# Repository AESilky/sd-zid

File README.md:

# Z80 Utilities (primarily a Disassembler)

Structured to be used as a Git Module, this repository contains various Z80 utilities, with the primary utility being the Disassembler.

## Disassembler

The disassembler processes Z80 opcode and additional memory reads into Z80 source. The process is controlled by an external routine,
meaning that the disassembler accepts byte values from the external routine and indicates if more bytes are needed. It does not access
memory or file data on its own. This makes it extremely flexible in how it is integrated into a system or utility program.

A test program is provided that will feed all instructions to the disassembler and output the result to standard output. It also
accepts command line options to just disassemble selected instruction groups (single-byte, CB, DD, ED, or FD) or use byte data included
on the command line.

The test program can be used as an example to integrate the disassembler into a system.

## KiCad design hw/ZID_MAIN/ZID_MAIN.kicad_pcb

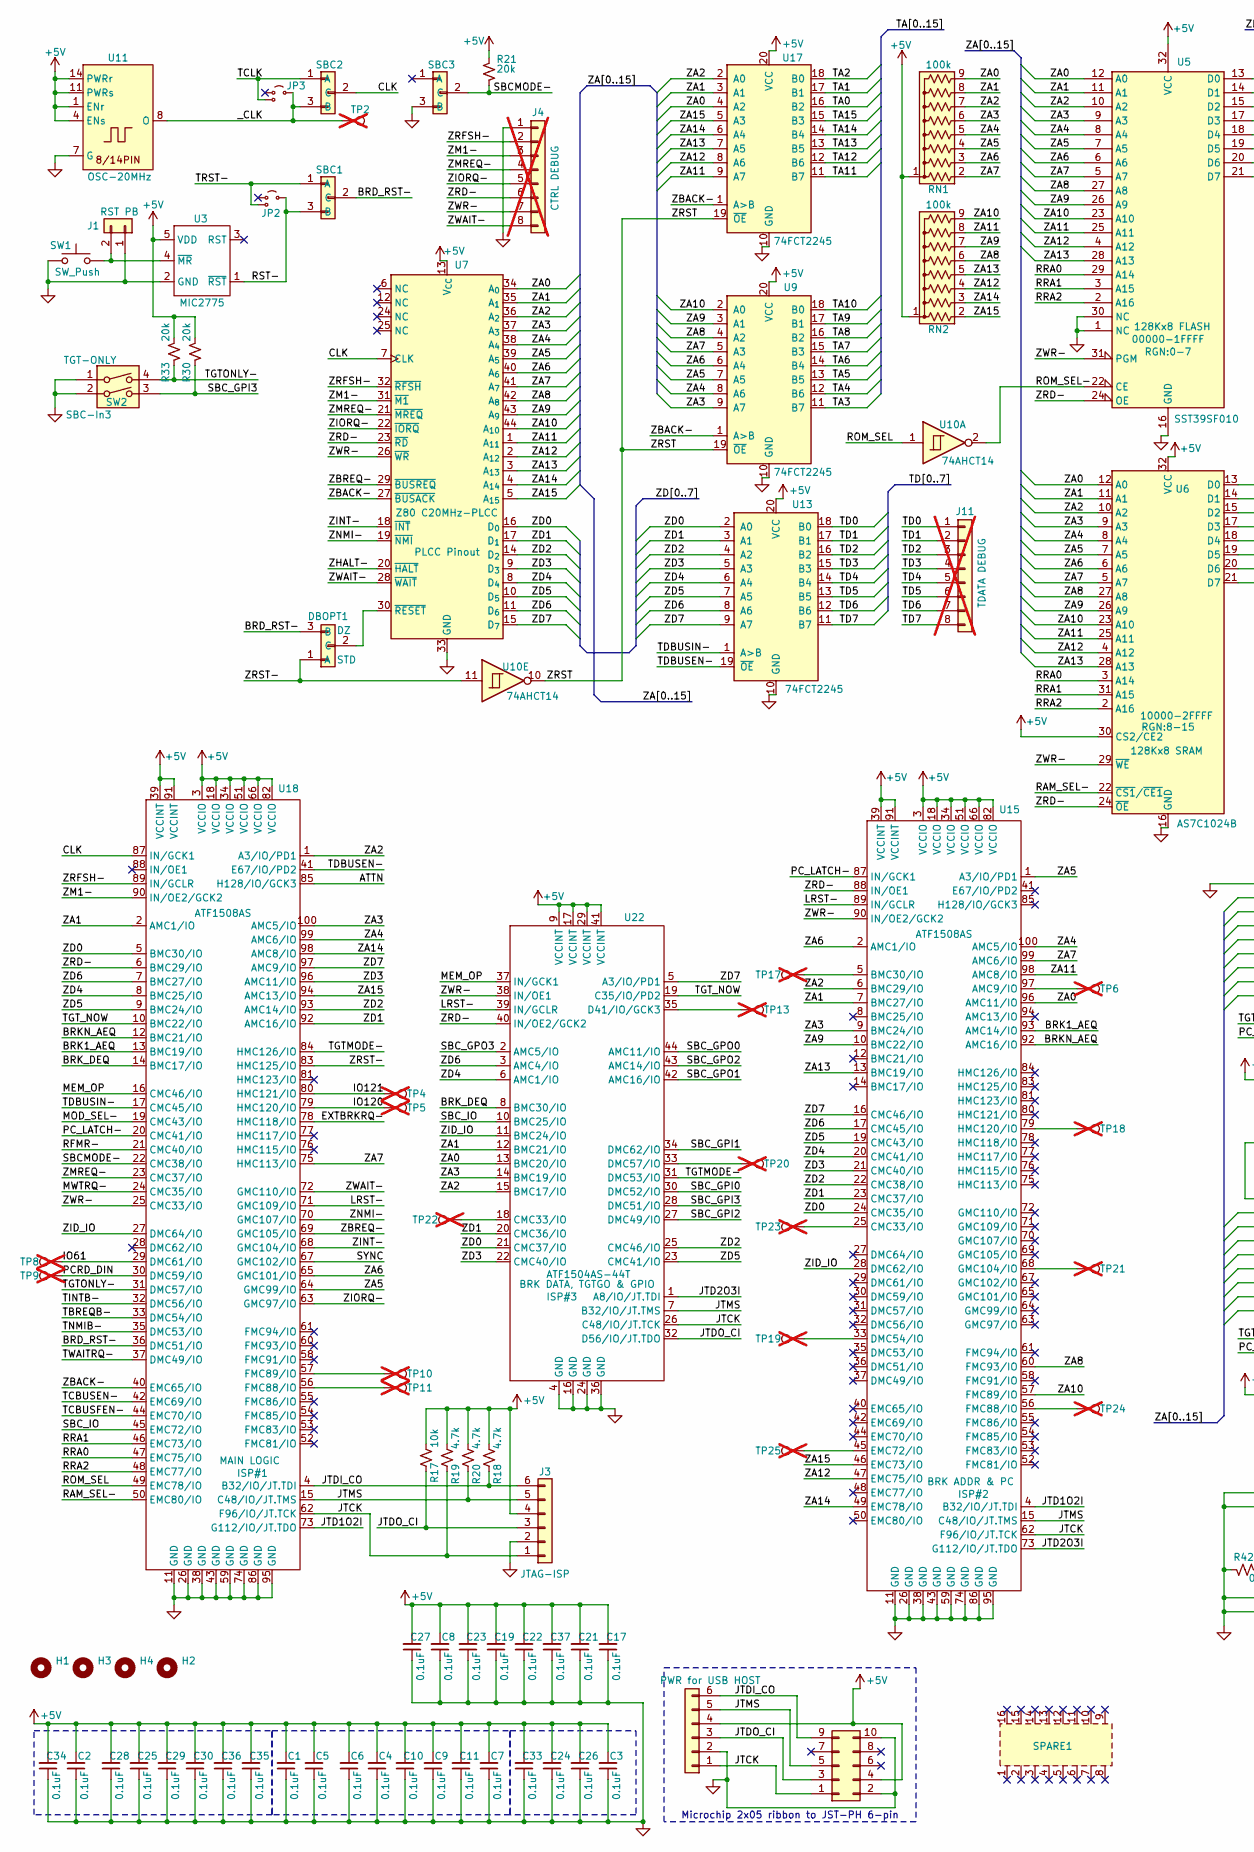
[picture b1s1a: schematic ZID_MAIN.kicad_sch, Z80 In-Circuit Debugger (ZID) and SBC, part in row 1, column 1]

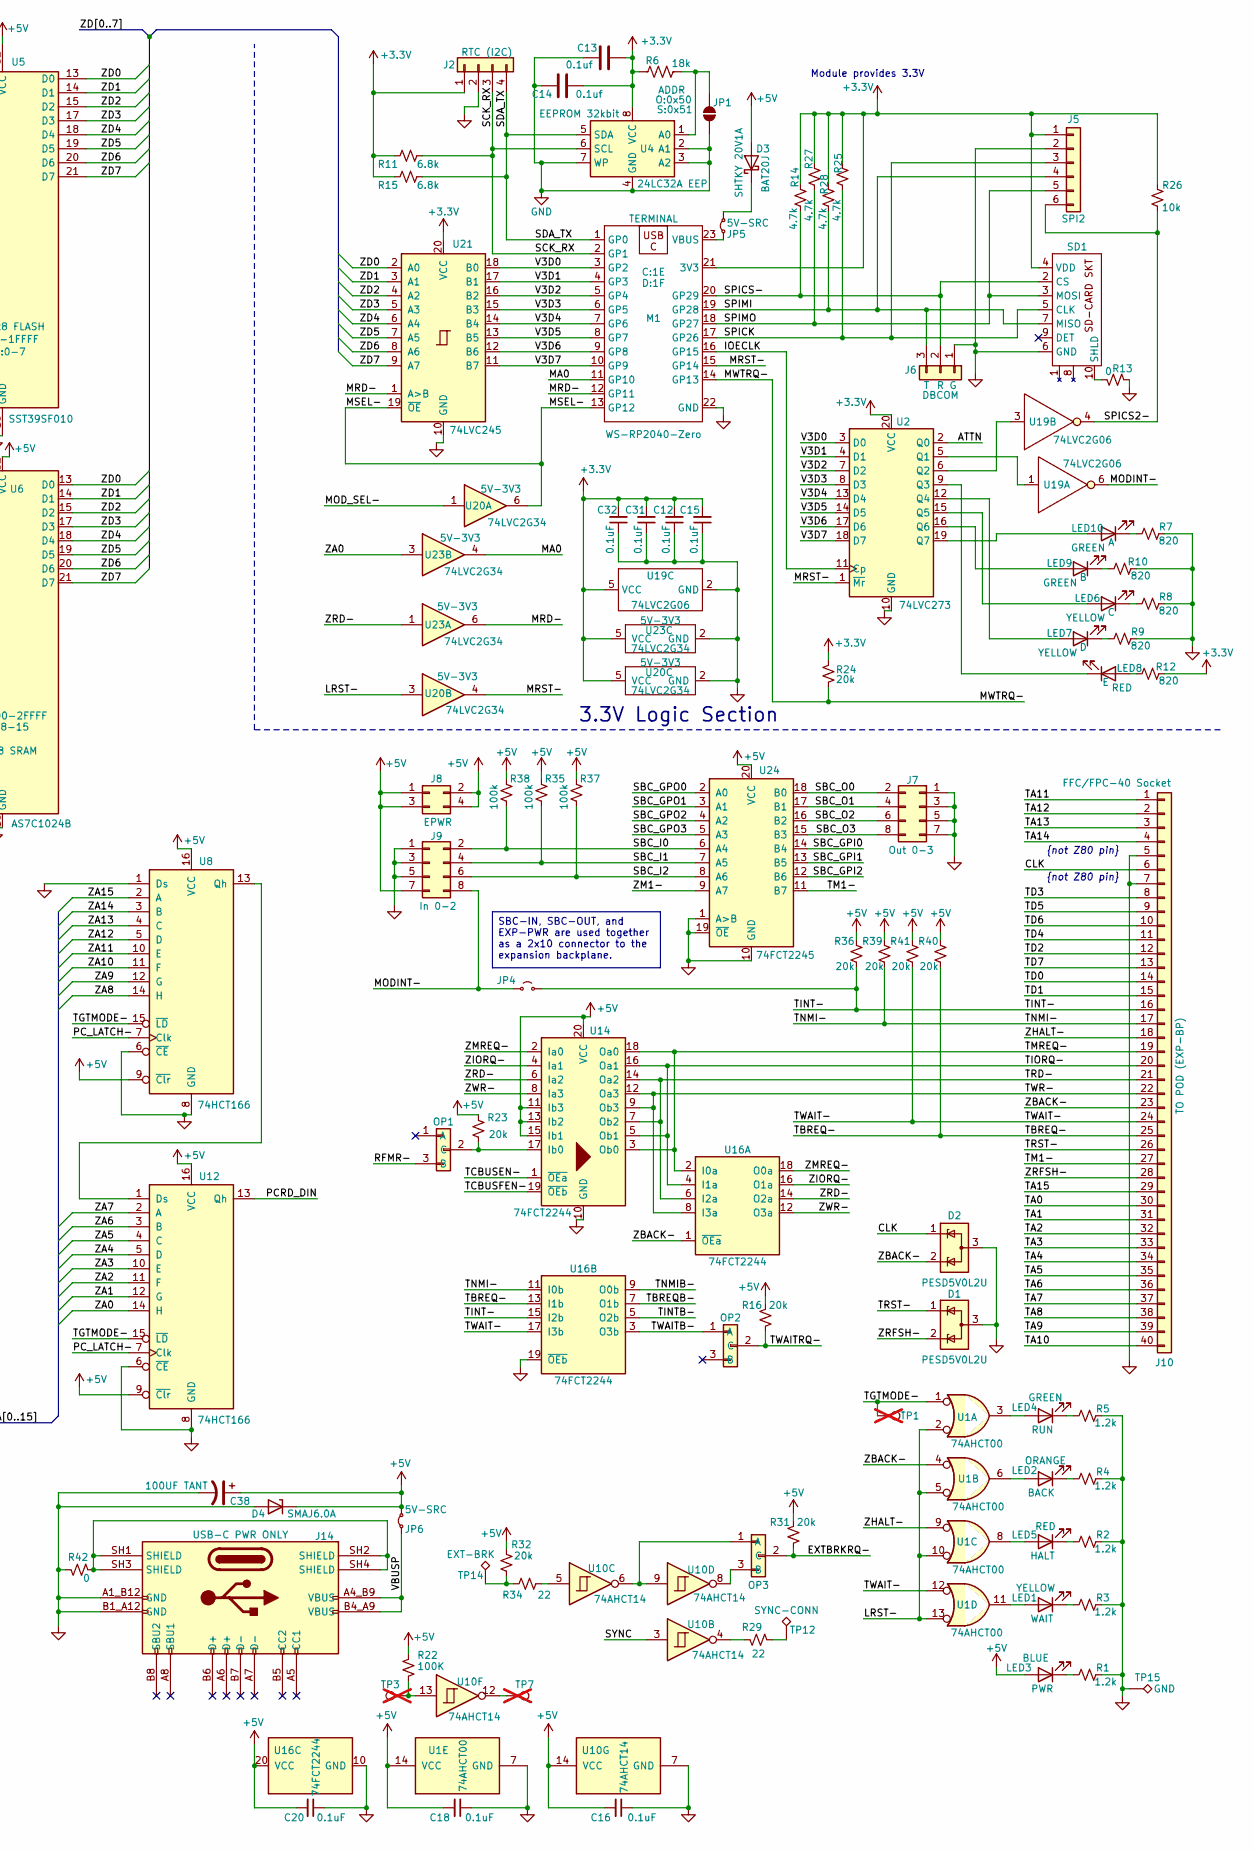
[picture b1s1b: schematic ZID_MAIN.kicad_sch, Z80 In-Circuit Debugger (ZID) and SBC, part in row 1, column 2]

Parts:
C1, C2, C3, C4, C5, C6, C7, C8, C9, C10, C11, C12, C15, C16, C17, C18, C19, C20, C21, C22, C23, C24, C25, C26, C27, C28, C29, C30, C31, C32, C33, C34, C35, C36, C37: 0.1uF; C_0603_1608Metric
C13, C14: 0.1uf; C_0603_1608Metric
C38: 100UF TANT; CP_EIA-7343-31_Kemet-D_HandSolder
D1, D2: PESD5V0L2U; SOT-323_SC-70
D3: BAT20J; D_SOD-323_HandSoldering
D4: SMAJ6.0A; D_SMA
DBOPT1: AES-Option_A-B_2mm; PinHeader_1x03_P2.00mm_Vertical
H1, H2, H3, H4: MountingHole; MountingHole_3.2mm_M3
J1: Conn 1x02 0.1" pin; PinHeader_1x02_P2.54mm_Vertical
J2: Conn 1x04 0.1" Socket; PinSocket_1x04_P2.54mm_Vertical; Part Ada-DS3231/PCF8523 RTC
J3, J5: JST-PH-K B6B; JST_PH_B6B-PH-K_1x06_P2.00mm_Vertical
J4, J11: Conn 1x08 0.1" pin; PinHeader_1x08_P2.54mm_Vertical; not fitted
J6: Conn 1x03 0.1" pin; PinHeader_1x03_P2.54mm_Vertical
J7, J9: Conn 2x04 0.1" pin; PinHeader_2x04_P2.54mm_Vertical
J8: Conn 2x02 0.1" pin; PinHeader_2x02_P2.54mm_Vertical
J10: FFC/FPC-40 Socket; CviLux_CF25401D0-05-NH_FFC-FPC-AES
J12, J14: USB-C PWR ONLY; AES-USB_C-Molex-BdTopMnt-2171790001
J13: Conn_02x05_PINHDR_2.54mm; IDC-Header_2x05_P2.54mm_Vertical
JP1: SolderJumper_2_Open; SolderJumper-2_P1.3mm_Open_RoundedPad1.0x1.5mm
JP2, JP3: Jumper_2_Small_Open_wsto-AES; PinHeader_1x03_P2.00mm_Vertical
JP4: Jumper_2_Small_Open; PinHeader_1x02_P2.00mm_Vertical
JP5, JP6: Jumper_2_Small_Bridged; PinHeader_1x02_P2.00mm_Vertical
LED1, LED6, LED7: LED YELLOW; LED_0805_2012Metric
LED2: LED ORANGE; LED_0805_2012Metric
LED3: LED BLUE; LED_0805_2012Metric
LED4, LED9, LED10: LED GREEN; LED_0805_2012Metric
LED5, LED8: LED RED; LED_0805_2012Metric
M1: WS-RP2040-Zero; RP2040_WS-ZERO-AES
OP1: AES-Option_A-B_2mm; PinHeader_1x03_P2.00mm_Vertical
OP2, OP3: pin header 1x03 0.1"; PinHeader_1x03_P2.54mm_Vertical
R1, R2, R3, R4, R5: 1.2k; R_0805_2012Metric
R6: 18k; R_0805_2012Metric
R7, R8, R9, R10, R12: 820; R_0805_2012Metric
R11, R15: 6.8k; R_0805_2012Metric
R13, R42: 0; R_0805_2012Metric
R14, R18, R19, R20, R25, R27, R28: 4.7k; R_0805_2012Metric
R16, R21, R23, R24, R30, R31, R32, R33, R36, R39, R40, R41: 20k; R_0805_2012Metric
R17, R26: 10k; R_0805_2012Metric
R22: 100K; R_0805_2012Metric
R29, R34: 22; R_0805_2012Metric
R35, R37, R38: 100k; R_0805_2012Metric
RN1, RN2: 100k; R_Array_SIP9
SBC1, SBC2, SBC3: AES-Option_A-B_2mm; PinHeader_1x03_P2.00mm_Vertical
SD1: SD-CARD Socket; AES-SDCard-GCT_MEM2075-00-140-01-A
SPARE1: SPARE-16-SOT-5_6-AES
SW1: SW_Push; AES-SW_PUSH_SMD_1P1T_NO_45x45mm-CK
SW2: SW_DIP_x02; SW_DIP_SPSTx02_Piano_CTS_Series194-2MSTN_W7.62mm_P2.54mm
TP1: TestPoint; PinHeader_1x01_P2.54mm_Vertical; not fitted
TP2: TestPoint; PinHeader_1x01_P2.00mm_Vertical; not fitted
TP3, TP4, TP5, TP6, TP7, TP8, TP9, TP10, TP11, TP13, TP17, TP18, TP19, TP20, TP21, TP22, TP23, TP24, TP25: TestPoint; TestPoint_THTPad_D1.0mm_Drill0.5mm; not fitted
TP12: SYNC-CONN; PinHeader_1x01_P2.54mm_Vertical
TP14: EXT-BRK; PinHeader_1x01_P2.54mm_Vertical
TP15: GND-CONN; PinHeader_1x01_P2.54mm_Vertical
U1: 74AHCT00; SO-14_3.9x8.65mm_P1.27mm
U2: 74LVC273; SO-20_12.8x7.5mm_P1.27mm
U3: MIC2775; SOT-23-5
U4: 24LC32A EEP; SOIC-8_3.9x4.9mm_P1.27mm
U5: SST39SF010; DIP-32_W15.24mm_Socket_LongPads
U6: AS7C1024B; SOJ-32_WN-AES
U7: Z80 C20MHz-PLCC; PLCC-44_THT-Socket
U8, U12: 74HCT166; SOIC-16_3.9x9.9mm_P1.27mm
U9, U13, U17, U24: 74FCT2245; SSOP-20_3.9x8.7mm_P0.635mm
U10: 74AHCT14; SO-14_3.9x8.65mm_P1.27mm
U11: OSC-20MHz; OSC-8_14-CO-AES
U14, U16: 74FCT2244; SSOP-20_3.9x8.7mm_P0.635mm
U15, U18: ATF1508AS; TQFP-100_14x14mm_P0.5mm
U19: 74LVC2G06; SOT-363_SC-70-6
U20, U23: 74LVC2G34; SOT-23-6
U21: 74LVC245; SO-20_5.3x12.6mm_P1.27mm
U22: ATF1504AS-44T; TQFP-44_10x10mm_P0.8mm

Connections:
+3.3V: C12.2, C13.1, C14.2, C15.2, C31.2, C32.2, J2.1, J5.1, M1.21 (3V3), R6.1, R11.2, R12.2, R14.2, R15.2, R24.1, R25.2, R26.2, R27.2, R28.2, SD1.4 (VDD), U2.20 (VCC), U4.8 (VCC), U19.5 (VCC), U20.5 (VCC), U21.20 (VCC), U23.5 (VCC)
+5V: C1.2, C2.2, C3.2, C4.2, C5.2, C6.2, C7.2, C8.2, C9.2, C10.2, C11.2, C16.2, C17.2, C18.2, C19.2, C20.2, C21.2, C22.2, C23.2, C24.2, C25.2, C26.2, C27.2, C28.2, C29.2, C30.2, C33.2, C34.2, C35.2, C36.2, C37.2, C38.1, D3.2 (A), D4.1 (K), J3.4, J8.1, J8.2, J8.3, J8.4, J9.7, J12.4, J13.4, JP6.2 (B), LED3.2 (A), R16.2, R17.1, R18.1, R19.1, R20.1, R21.2, R22.2, R23.2, R30.1, R31.2, R32.1, R33.1, R35.1, R36.1, R37.1, R38.1, R39.1, R40.1, R41.1, RN1.1 (common), RN2.1 (common), U1.14 (VCC), U3.5 (VDD), U5.32 (VCC), U6.30 (CS2/CE2), U6.32 (VCC), U7.13 (V_{CC}), U8.9 (~Clr), U8.16 (VCC), U9.20 (VCC), U10.14 (VCC), U11.1 (ENr), U11.4 (ENs), U11.11 (PWRs), U11.14 (PWRr), U12.9 (~Clr), U12.16 (VCC), U13.20 (VCC), U14.11 (Ib3), U14.13 (Ib2), U14.15 (Ib1), U14.20 (VCC), U15.3 (VCCIO), U15.18 (VCCIO), U15.34 (VCCIO), U15.39 (VCCINT), U15.51 (VCCIO), U15.66 (VCCIO), U15.82 (VCCIO), U15.91 (VCCINT), U16.20 (VCC), U17.20 (VCC), U18.3 (VCCIO), U18.18 (VCCIO), U18.34 (VCCIO), U18.39 (VCCINT), U18.51 (VCCIO), U18.66 (VCCIO), U18.82 (VCCIO), U18.91 (VCCINT), U22.9 (VCCINT), U22.17 (VCCINT), U22.29 (VCCINT), U22.41 (VCCINT), U24.20 (VCC)
/ATTN: U2.2 (Q0), U18.85 (H128/IO/GCK3)
/BRD_RST-: DBOPT1.3 (B), SBC1.2 (C), U18.36 (DMC51/IO)
/BRK1_AEQ: U15.93 (AMC14/IO), U18.13 (BMC19/IO)
/BRKN_AEQ: U15.92 (AMC16/IO), U18.12 (BMC21/IO)
/BRK_DEQ: U18.14 (BMC17/IO), U22.8 (BMC30/IO)
/CLK: D2.1 (K), J10.6, SBC2.2 (C), U7.7 (CLK), U18.87 (IN/GCK1)
/EXTBRKRQ-: OP3.2 (C), R31.1, U18.78 (HMC118/IO)
/IO61: TP8.1, U18.29 (DMC61/IO)
/IO120: TP5.1, U18.79 (HMC120/IO)
/IO121: TP4.1, U18.80 (HMC121/IO)
/IOECLK: M1.16 (GP15), U2.11 (Cp)
/JTCK: J3.1, J12.1, J13.1, R19.2, U15.62 (F96/IO/JT.TCK), U18.62 (F96/IO/JT.TCK), U22.26 (C48/IO/JT.TCK)
/JTD1O2I: U15.4 (B32/IO/JT.TDI), U18.73 (G112/IO/JT.TDO)
/JTD2O3I: U15.73 (G112/IO/JT.TDO), U22.1 (A8/IO/JT.TDI)
/JTDI_CO: J3.6, J12.6, J13.9, R18.2, U18.4 (B32/IO/JT.TDI)
/JTDO_CI: J3.3, J12.3, J13.3, R17.2, U22.32 (D56/IO/JT.TDO)
/JTMS: J3.5, J12.5, J13.5, R20.2, U15.15 (C48/IO/JT.TMS), U18.15 (C48/IO/JT.TMS), U22.7 (B32/IO/JT.TMS)
/LRST-: U1.2, U1.5, U1.10, U1.13, U15.89 (IN/GCLR), U18.71 (GMC109/IO), U20.3, U22.39 (IN/GCLR)
/MA0: M1.11 (GP10), U23.4
/MEM_OP: U18.16 (CMC46/IO), U22.37 (IN/GCK1)
/MODINT-: J9.8, JP4.1 (A), U19.6
/MOD_SEL-: U18.19 (CMC43/IO), U20.1
/MRD-: M1.12 (GP11), U21.1 (A>B), U23.6
/MRST-: M1.15 (GP14), U2.1 (~Mr), U20.4
/MSEL-: M1.13 (GP12), U20.6, U21.19 (~OE)
/MWTRQ-: M1.14 (GP13), R24.2, U18.24 (CMC35/IO)
/PCRD_DIN: TP9.1, U12.13 (Qh), U18.30 (DMC59/IO)
/PC_LATCH-: U8.7 (Clk), U12.7 (Clk), U15.87 (IN/GCK1), U18.20 (CMC41/IO)
/RAM_SEL-: U6.22 (~CS1/~CE1), U18.50 (EMC80/IO)
/RFMR-: OP1.3 (B), U18.21 (CMC40/IO)
/ROM_SEL: U10.1, U18.49 (EMC78/IO)
/ROM_SEL-: U5.22 (CE), U10.2
/RRA0: U5.29 (A14), U6.3 (A14), U18.47 (EMC75/IO)
/RRA1: U5.3 (A15), U6.31 (A15), U18.46 (EMC73/IO)
/RRA2: U5.2 (A16), U6.2 (A16), U18.48 (EMC77/IO)
/RST-: JP2.2 (B), SBC1.3 (B), U3.1 (~RST)
/SBCMODE-: R21.1, SBC3.2 (C), U18.22 (CMC38/IO)
/SBC_GPI0: U22.30 (DMC52/IO), U24.14 (B4)
/SBC_GPI1: U22.34 (DMC62/IO), U24.13 (B5)
/SBC_GPI2: U22.27 (DMC49/IO), U24.12 (B6)
/SBC_GPI3: R30.2, SW2.3, U22.28 (DMC51/IO)
/SBC_GPO0: U22.44 (AMC11/IO), U24.2 (A0)
/SBC_GPO1: U22.42 (AMC16/IO), U24.3 (A1)
/SBC_GPO2: U22.43 (AMC14/IO), U24.4 (A2)
/SBC_GPO3: U22.2 (AMC5/IO), U24.5 (A3)
/SBC_I0: J9.2, R38.2, U24.6 (A4)
/SBC_I1: J9.4, R35.2, U24.7 (A5)
/SBC_I2: J9.6, R37.2, U24.8 (A6)
/SBC_IO: U18.45 (EMC72/IO), U22.10 (BMC25/IO)
/SBC_O0: J7.2, U24.18 (B0)
/SBC_O1: J7.4, U24.17 (B1)
/SBC_O2: J7.6, U24.16 (B2)
/SBC_O3: J7.8, U24.15 (B3)
/SCK_RX: J2.3, M1.2 (GP1), R11.1, U4.6 (SCL)
/SDA_TX: J2.4, M1.1 (GP0), R15.1, U4.5 (SDA)
/SPICK: J5.3, M1.17 (GP26), R25.1, SD1.5 (CLK)
/SPICS2-: J5.6, R26.1, U19.4
/SPICS-: J6.2, M1.20 (GP29), R14.1, SD1.2 (CS)
/SPIMI: J5.4, J6.3, M1.19 (GP28), R28.1, SD1.7 (MISO)
/SPIMO: J5.5, M1.18 (GP27), R27.1, SD1.3 (MOSI)
/SYNC: U10.3, U18.67 (GMC102/IO)
/TA0: J10.30, U17.16 (B2)
/TA1: J10.31, U17.17 (B1)
/TA2: J10.32, U17.18 (B0)
/TA3: J10.33, U9.11 (B7)
/TA4: J10.34, U9.12 (B6)
/TA5: J10.35, U9.13 (B5)
/TA6: J10.36, U9.14 (B4)
/TA7: J10.37, U9.15 (B3)
/TA8: J10.38, U9.16 (B2)
/TA9: J10.39, U9.17 (B1)
/TA10: J10.40, U9.18 (B0)
/TA11: J10.1, U17.11 (B7)
/TA12: J10.2, U17.12 (B6)
/TA13: J10.3, U17.13 (B5)
/TA14: J10.4, U17.14 (B4)
/TA15: J10.29, U17.15 (B3)
/TBREQ-: J10.25, R40.2, U16.13 (I1b)
/TBREQB-: U16.7 (O1b), U18.33 (DMC54/IO)
/TCBUSEN-: U14.1 (~OEa), U18.42 (EMC69/IO)
/TCBUSFEN-: U14.19 (~OEb), U18.44 (EMC70/IO)
/TCLK: JP3.3 (C), SBC2.1 (A)
/TD0: J10.14, J11.1, U13.18 (B0)
/TD1: J10.15, J11.2, U13.17 (B1)
/TD2: J10.12, J11.3, U13.16 (B2)
/TD3: J10.8, J11.4, U13.15 (B3)
/TD4: J10.11, J11.5, U13.14 (B4)
/TD5: J10.9, J11.6, U13.13 (B5)
/TD6: J10.10, J11.7, U13.12 (B6)
/TD7: J10.13, J11.8, U13.11 (B7)
/TDBUSEN-: U13.19 (~OE), U18.41 (E67/IO/PD2)
/TDBUSIN-: U13.1 (A>B), U18.17 (CMC45/IO)
/TGTMODE-: TP1.1, U1.1, U8.15 (~LD), U12.15 (~LD), U18.84 (HMC126/IO), U22.31 (DMC53/IO)
/TGTONLY-: R33.2, SW2.4, U18.31 (DMC57/IO)
/TGT_NOW: U18.10 (BMC22/IO), U22.19 (C35/IO/PD2)
/TINT-: J10.16, JP4.2 (B), R36.2, U16.15 (I2b)
/TINTB-: U16.5 (O2b), U18.32 (DMC56/IO)
/TIORQ-: J10.20, U14.5 (Ob1), U14.16 (Oa1), U16.4 (I1a)
/TM1-: J10.27, U24.11 (B7)
/TMREQ-: J10.19, U14.3 (Ob0), U14.18 (Oa0), U16.2 (I0a)
/TNMI-: J10.17, R39.2, U16.11 (I0b)
/TNMIB-: U16.9 (O0b), U18.35 (DMC53/IO)
/TRD-: J10.21, U14.7 (Ob2), U14.14 (Oa2), U16.6 (I2a)
/TRST-: D1.1 (K), J10.26, JP2.3 (C), SBC1.1 (A)
/TWAIT-: J10.24, R41.2, U1.12, U16.17 (I3b)
/TWAITB-: OP2.1 (A), U16.3 (O3b)
/TWAITRQ-: OP2.2 (C), R16.1, U18.37 (DMC49/IO)
/TWR-: J10.22, U14.9 (Ob3), U14.12 (Oa3), U16.8 (I3a)
/V3D0: M1.3 (GP2), U2.3 (D0), U21.18 (B0)
/V3D1: M1.4 (GP3), U2.4 (D1), U21.17 (B1)
/V3D2: M1.5 (GP4), U2.7 (D2), U21.16 (B2)
/V3D3: M1.6 (GP5), U2.8 (D3), U21.15 (B3)
/V3D4: M1.7 (GP6), U2.13 (D4), U21.14 (B4)
/V3D5: M1.8 (GP7), U2.14 (D5), U21.13 (B5)
/V3D6: M1.9 (GP8), U2.17 (D6), U21.12 (B6)
/V3D7: M1.10 (GP9), U2.18 (D7), U21.11 (B7)
/VBUSP: J14.A4_B9 (VBUS), J14.B4_A9 (VBUS), JP6.1 (A)
/ZA0: RN1.9 (R8), U5.12 (A0), U6.12 (A0), U7.34 (A_{0}), U12.14 (H), U15.96 (AMC11/IO), U17.4 (A2), U22.13 (BMC20/IO), U23.3
/ZA1: RN1.8 (R7), U5.11 (A1), U6.11 (A1), U7.35 (A_{1}), U12.12 (G), U15.7 (BMC27/IO), U17.3 (A1), U18.2 (AMC1/IO), U22.12 (BMC21/IO)
/ZA2: RN1.7 (R6), U5.10 (A2), U6.10 (A2), U7.36 (A_{2}), U12.11 (F), U15.6 (BMC29/IO), U17.2 (A0), U18.1 (A3/IO/PD1), U22.15 (BMC17/IO)
/ZA3: RN1.6 (R5), U5.9 (A3), U6.9 (A3), U7.37 (A_{3}), U9.9 (A7), U12.10 (E), U15.9 (BMC24/IO), U18.100 (AMC5/IO), U22.14 (BMC19/IO)
/ZA4: RN1.5 (R4), U5.8 (A4), U6.8 (A4), U7.38 (A_{4}), U9.8 (A6), U12.5 (D), U15.100 (AMC5/IO), U18.99 (AMC6/IO)
/ZA5: RN1.4 (R3), U5.7 (A5), U6.7 (A5), U7.39 (A_{5}), U9.7 (A5), U12.4 (C), U15.1 (A3/IO/PD1), U18.64 (GMC99/IO)
/ZA6: RN1.3 (R2), U5.6 (A6), U6.6 (A6), U7.40 (A_{6}), U9.6 (A4), U12.3 (B), U15.2 (AMC1/IO), U18.65 (GMC101/IO)
/ZA7: RN1.2 (R1), U5.5 (A7), U6.5 (A7), U7.41 (A_{7}), U9.5 (A3), U12.2 (A), U15.99 (AMC6/IO), U18.75 (HMC113/IO)
/ZA8: RN2.6 (R5), U5.27 (A8), U6.27 (A8), U7.42 (A_{8}), U8.14 (H), U9.4 (A2), U15.60 (FMC93/IO)
/ZA9: RN2.7 (R6), U5.26 (A9), U6.26 (A9), U7.43 (A_{9}), U8.12 (G), U9.3 (A1), U15.10 (BMC22/IO)
/ZA10: RN2.9 (R8), U5.23 (A10), U6.23 (A10), U7.44 (A_{10}), U8.11 (F), U9.2 (A0), U15.57 (FMC89/IO)
/ZA11: RN2.8 (R7), U5.25 (A11), U6.25 (A11), U7.1 (A_{11}), U8.10 (E), U15.98 (AMC8/IO), U17.9 (A7)
/ZA12: RN2.4 (R3), U5.4 (A12), U6.4 (A12), U7.2 (A_{12}), U8.5 (D), U15.47 (EMC75/IO), U17.8 (A6)
/ZA13: RN2.5 (R4), U5.28 (A13), U6.28 (A13), U7.3 (A_{13}), U8.4 (C), U15.13 (BMC19/IO), U17.7 (A5)
/ZA14: RN2.3 (R2), U7.4 (A_{14}), U8.3 (B), U15.49 (EMC78/IO), U17.6 (A4), U18.98 (AMC8/IO)
/ZA15: RN2.2 (R1), U7.5 (A_{15}), U8.2 (A), U15.46 (EMC73/IO), U17.5 (A3), U18.94 (AMC13/IO)
/ZBACK-: D2.2 (K), J10.23, U1.4, U7.27 (~BUSACK), U9.1 (A>B), U16.1 (~OEa), U17.1 (A>B), U18.40 (EMC65/IO)
/ZBREQ-: U7.29 (~BUSREQ), U18.69 (GMC105/IO)
/ZD0: U5.13 (D0), U6.13 (D0), U7.16 (D_{0}), U13.2 (A0), U15.24 (CMC35/IO), U18.5 (BMC30/IO), U21.2 (A0), U22.21 (CMC37/IO)
/ZD1: U5.14 (D1), U6.14 (D1), U7.17 (D_{1}), U13.3 (A1), U15.23 (CMC37/IO), U18.92 (AMC16/IO), U21.3 (A1), U22.20 (CMC36/IO)
/ZD2: U5.15 (D2), U6.15 (D2), U7.14 (D_{2}), U13.4 (A2), U15.22 (CMC38/IO), U18.93 (AMC14/IO), U21.4 (A2), U22.25 (CMC46/IO)
/ZD3: U5.17 (D3), U6.17 (D3), U7.9 (D_{3}), U13.5 (A3), U15.21 (CMC40/IO), U18.96 (AMC11/IO), U21.5 (A3), U22.22 (CMC40/IO)
/ZD4: U5.18 (D4), U6.18 (D4), U7.8 (D_{4}), U13.6 (A4), U15.20 (CMC41/IO), U18.8 (BMC25/IO), U21.6 (A4), U22.6 (AMC1/IO)
/ZD5: U5.19 (D5), U6.19 (D5), U7.10 (D_{5}), U13.7 (A5), U15.19 (CMC43/IO), U18.9 (BMC24/IO), U21.7 (A5), U22.23 (CMC41/IO)
/ZD6: U5.20 (D6), U6.20 (D6), U7.11 (D_{6}), U13.8 (A6), U15.17 (CMC45/IO), U18.7 (BMC27/IO), U21.8 (A6), U22.3 (AMC4/IO)
/ZD7: U5.21 (D7), U6.21 (D7), U7.15 (D_{7}), U13.9 (A7), U15.16 (CMC46/IO), U18.97 (AMC9/IO), U21.9 (A7), U22.5 (A3/IO/PD1)
/ZHALT-: J10.18, U1.9, U7.20 (~HALT)
/ZID_IO: U15.28 (DMC62/IO), U18.27 (DMC64/IO), U22.11 (BMC24/IO)
/ZINT-: U7.18 (~INT), U18.68 (GMC104/IO)
/ZIORQ-: J4.5, U7.22 (~IORQ), U14.4 (Ia1), U16.16 (O1a), U18.63 (GMC97/IO)
/ZM1-: J4.3, U7.31 (~M1), U18.90 (IN/OE2/GCK2), U24.9 (A7)
/ZMREQ-: J4.4, U7.21 (~MREQ), U14.2 (Ia0), U16.18 (O0a), U18.23 (CMC37/IO)
/ZNMI-: U7.19 (~NMI), U18.70 (GMC107/IO)
/ZRD-: J4.6, U5.24 (OE), U6.24 (~OE), U7.23 (~RD), U14.6 (Ia2), U15.88 (IN/OE1), U16.14 (O2a), U18.6 (BMC29/IO), U22.40 (IN/OE2/GCK2), U23.1
/ZRFSH-: D1.2 (K), J4.2, J10.28, U7.32 (~RFSH), U18.89 (IN/GCLR)
/ZRST: U9.19 (~OE), U10.10, U17.19 (~OE)
/ZRST-: DBOPT1.1 (A), U10.11, U18.83 (HMC125/IO)
/ZWAIT-: J4.8, U7.28 (~WAIT), U18.72 (GMC110/IO)
/ZWR-: J4.7, U5.31 (PGM), U6.29 (~WE), U7.26 (~WR), U14.8 (Ia3), U15.90 (IN/OE2/GCK2), U16.12 (O3a), U18.25 (CMC33/IO), U22.38 (IN/OE1)
/_CLK: JP3.2 (B), SBC2.3 (B), TP2.1, U11.8 (O)
GND: C1.1, C2.1, C3.1, C4.1, C5.1, C6.1, C7.1, C8.1, C9.1, C10.1, C11.1, C12.1, C13.2, C14.1, C15.1, C16.1, C17.1, C18.1, C19.1, C20.1, C21.1, C22.1, C23.1, C24.1, C25.1, C26.1, C27.1, C28.1, C29.1, C30.1, C31.1, C32.1, C33.1, C34.1, C35.1, C36.1, C37.1, C38.2, D1.3 (A), D2.3 (A), D4.2 (A), J1.1, J2.2, J3.2, J4.1, J5.2, J6.1, J7.1, J7.3, J7.5, J7.7, J9.1, J9.3, J9.5, J10.5, J10.7, J12.2, J13.2, J13.10, J14.A1_B12 (GND), J14.B1_A12 (GND), JP1.1 (A), M1.22 (GND), R1.2, R2.2, R3.2, R4.2, R5.2, R7.2, R8.2, R9.2, R10.2, R13.1, R42.1, SBC3.3 (B), SD1.6 (GND), SW1.1, SW2.1, SW2.2, TP15.1, U1.7 (GND), U2.10 (GND), U3.2 (GND), U4.2 (A1), U4.3 (A2), U4.4 (GND), U4.7 (WP), U5.1 (NC), U5.16 (GND), U5.30 (NC), U6.16 (GND), U7.33 (GND), U8.1 (Ds), U8.6 (~CE), U8.8 (GND), U9.10 (GND), U10.7 (GND), U11.7 (G), U12.6 (~CE), U12.8 (GND), U13.10 (GND), U14.10 (GND), U15.11 (GND), U15.26 (GND), U15.38 (GND), U15.43 (GND), U15.59 (GND), U15.74 (GND), U15.86 (GND), U15.95 (GND), U16.10 (GND), U16.19 (~OEb), U17.10 (GND), U18.11 (GND), U18.26 (GND), U18.38 (GND), U18.43 (GND), U18.59 (GND), U18.74 (GND), U18.86 (GND), U18.95 (GND), U19.2 (GND), U20.2 (GND), U21.10 (GND), U22.4 (GND), U22.16 (GND), U22.24 (GND), U22.36 (GND), U23.2 (GND), U24.1 (A>B), U24.10 (GND), U24.19 (~OE)
unnamed: D3.1 (K), JP5.2 (B)
unnamed: DBOPT1.2 (C), U7.30 (~RESET)
unnamed: J1.2, SW1.2, U3.4 (~MR)
unnamed: J14.SH1 (SHIELD), J14.SH2 (SHIELD), J14.SH3 (SHIELD), J14.SH4 (SHIELD), R42.2
unnamed: JP1.2 (B), R6.2, U4.1 (A0)
unnamed: JP5.1 (A), M1.23 (VBUS)
unnamed: LED1.2 (A), U1.11
unnamed: LED1.1 (K), R3.1
unnamed: LED2.2 (A), U1.6
unnamed: LED2.1 (K), R4.1
unnamed: LED3.1 (K), R1.1
unnamed: LED4.2 (A), U1.3
unnamed: LED4.1 (K), R5.1
unnamed: LED5.2 (A), U1.8
unnamed: LED5.1 (K), R2.1
unnamed: LED6.2 (A), U2.15 (Q5)
unnamed: LED6.1 (K), R8.1
unnamed: LED7.2 (A), U2.12 (Q4)
unnamed: LED7.1 (K), R9.1
unnamed: LED8.2 (A), R12.1
unnamed: LED8.1 (K), U2.9 (Q3)
unnamed: LED9.2 (A), U2.16 (Q6)
unnamed: LED9.1 (K), R10.1
unnamed: LED10.2 (A), U2.19 (Q7)
unnamed: LED10.1 (K), R7.1
unnamed: OP1.2 (C), R23.1, U14.17 (Ib0)
unnamed: OP3.1 (A), U10.6, U10.9
unnamed: OP3.3 (B), U10.8
unnamed: R22.1, TP3.1, U10.13
unnamed: R29.1, TP12.1
unnamed: R29.2, U10.4
unnamed: R32.2, R34.1, TP14.1
unnamed: R34.2, U10.5
unnamed: R13.2, SD1.10 (SHLD)
unnamed: TP7.1, U10.12
unnamed: U2.5 (Q1), U19.1
unnamed: U2.6 (Q2), U19.3
unnamed: U8.13 (Qh), U12.1 (Ds)
unnamed: TP6.1, U15.97 (AMC9/IO)
unnamed: TP17.1, U15.5 (BMC30/IO)
unnamed: TP23.1, U15.25 (CMC33/IO)
unnamed: TP19.1, U15.33 (DMC54/IO)
unnamed: TP25.1, U15.45 (EMC72/IO)
unnamed: TP24.1, U15.56 (FMC88/IO)
unnamed: TP21.1, U15.68 (GMC104/IO)
unnamed: TP18.1, U15.79 (HMC120/IO)
unnamed: TP11.1, U18.56 (FMC88/IO)
unnamed: TP10.1, U18.57 (FMC89/IO)
unnamed: TP22.1, U22.18 (CMC33/IO)
unnamed: TP13.1, U22.35 (D41/IO/GCK3)
unnamed: TP20.1, U22.33 (DMC57/IO)

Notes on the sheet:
3.3V Logic Section
Module provides 3.3V
{not Z80 pin}
SBC-IN, SBC-OUT, and EXP-PWR are used together as a 2x10 connector to the expansion backplane.
Microchip 2x05 ribbon to JST-PH 6-pin

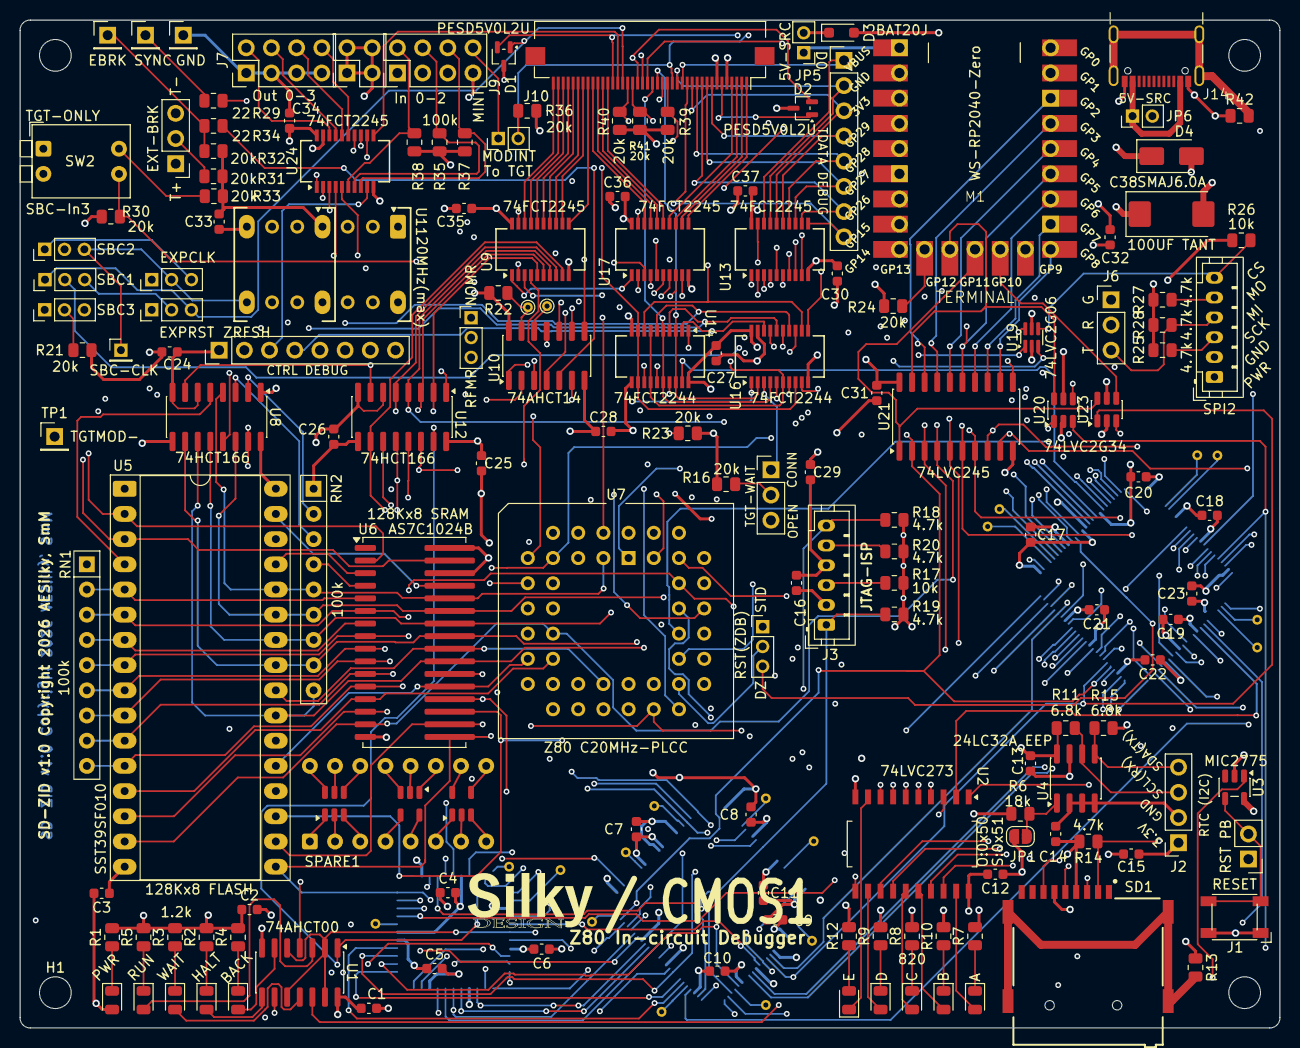
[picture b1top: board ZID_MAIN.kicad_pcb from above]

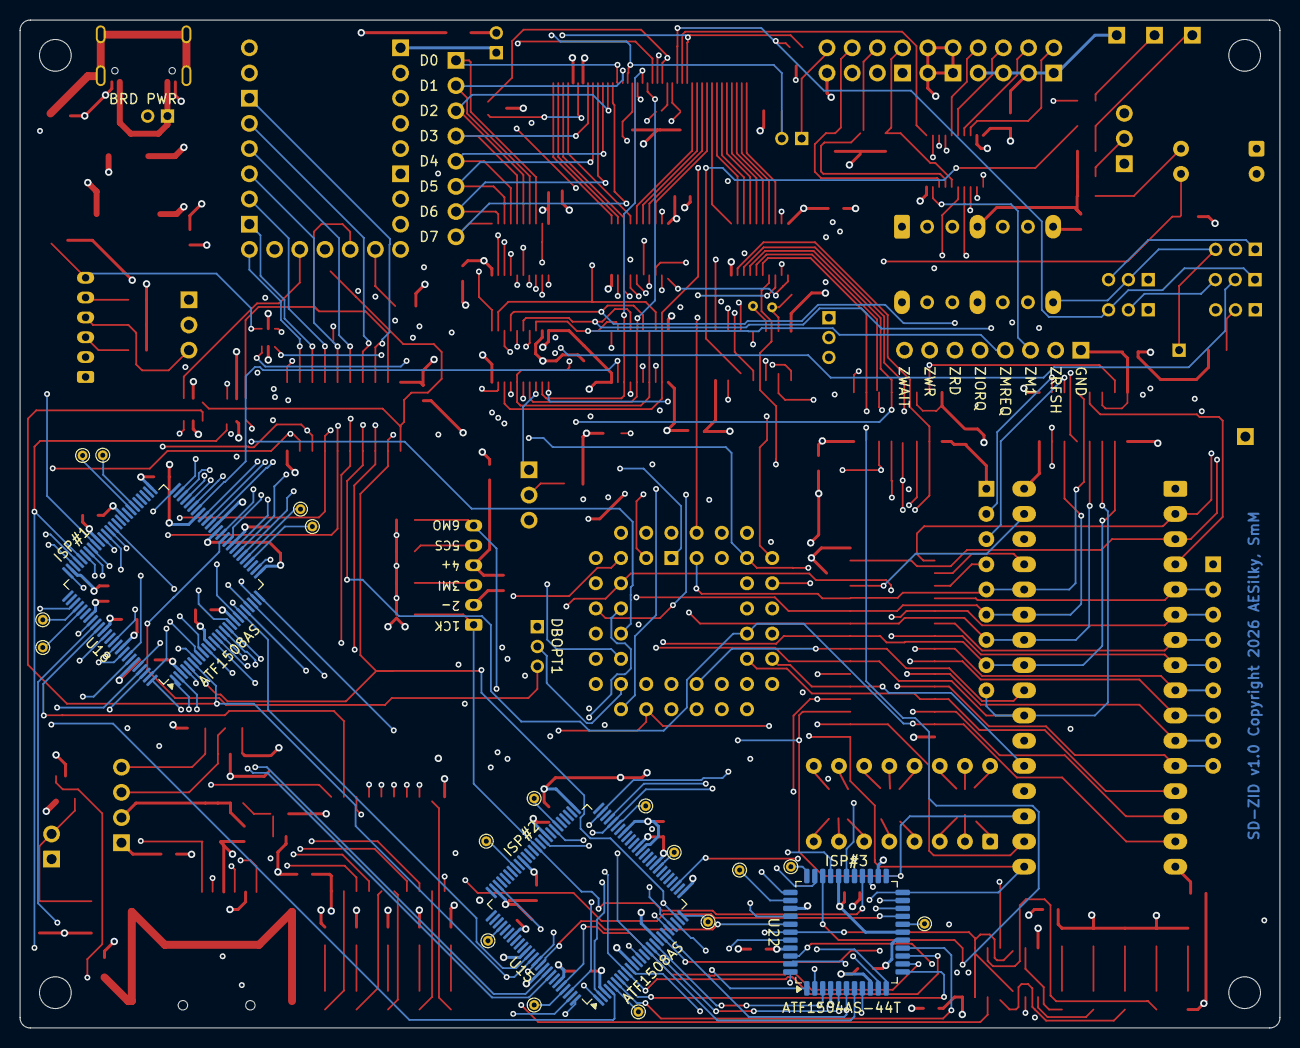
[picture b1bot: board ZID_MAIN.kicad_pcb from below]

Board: 6 copper layers, 127.0 x 101.6 mm, 178 parts (20 on the bottom side), 211 nets.

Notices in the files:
hw/ZID_EXP_BP/ZID_EXP_BP.kicad_pcb:
Copyright 2026 AESilky
hw/ZID_MAIN/ZID_MAIN.kicad_pcb:
Copyright 2026 AESilky, SmM
SD-ZID v1.0 Copyright 2026 AESilky, SmM
